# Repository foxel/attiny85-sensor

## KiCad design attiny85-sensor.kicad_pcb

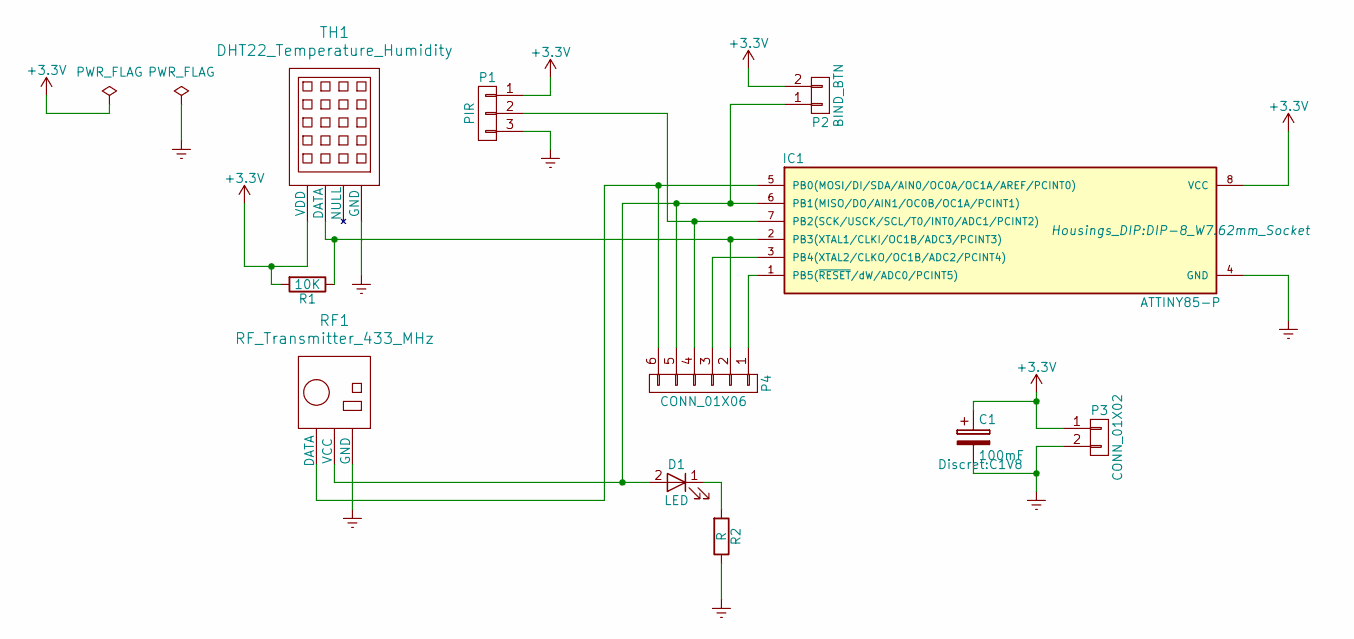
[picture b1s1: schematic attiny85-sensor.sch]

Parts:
C1: 100mF; C1V8
D1: LED; LED-3MM
IC1: ATTINY85-P; DIP-8_W7.62mm_Socket
P1: PIR; Pin_Header_Straight_1x03
P2: BIND_BTN; Pin_Header_Straight_1x02
P3: CONN_01X02; Pin_Header_Straight_1x02
P4: CONN_01X06; SMD_Pads
R1: 10K; R1
R2: R; R1
RF1: RF_Transmitter_433_MHz; RF_Transmitter_433_MHz_4PIN
TH1: DHT22_Temperature_Humidity

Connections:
+3V3: C1.1, IC1.8 (VCC), P1.1, P2.2, P3.1, R1.2, TH1.1 (VDD)
Earth: C1.2, IC1.4 (GND), P1.3, P3.2, R2.1, RF1.3 (GND), TH1.4 (GND)
unnamed: D1.1 (K), R2.2
unnamed: D1.2 (A), IC1.6 (PB1(MISO/DO/AIN1/OC0B/OC1A/PCINT1)), P2.1, P4.5, RF1.2 (VCC)
unnamed: IC1.1 (PB5(~RESET~/dW/ADC0/PCINT5)), P4.1
unnamed: IC1.2 (PB3(XTAL1/CLKI/OC1B/ADC3/PCINT3)), P4.2, R1.1, TH1.2 (DATA)
unnamed: IC1.3 (PB4(XTAL2/CLKO/OC1B/ADC2/PCINT4)), P4.3
unnamed: IC1.5 (PB0(MOSI/DI/SDA/AIN0/OC0A/OC1A/AREF/PCI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), P4.6, RF1.1 (DATA)
unnamed: IC1.7 (PB2(SCK/USCK/SCL/T0/INT0/ADC1/PCINT2)), P1.2, P4.4

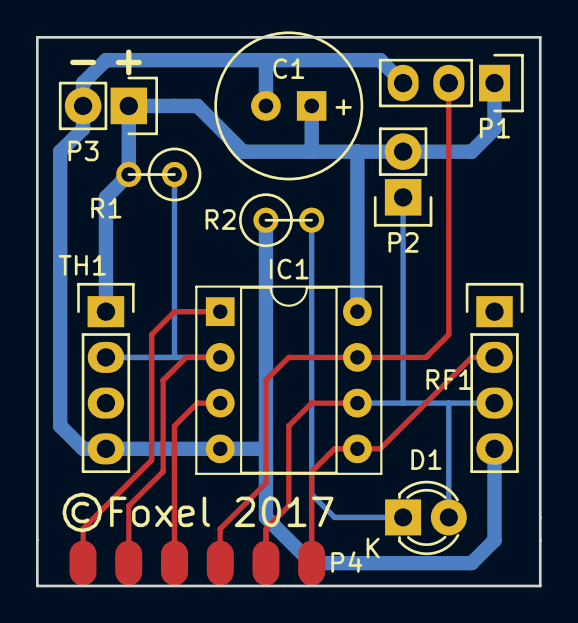
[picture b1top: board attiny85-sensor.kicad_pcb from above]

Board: 2 copper layers, 27.9 x 30.5 mm, 11 parts (0 on the bottom side), 9 nets.

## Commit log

2017-09-27 initial
2017-09-27 Socket for the chip
2019-01-05 Updated to comply newest library - stability fix
2019-01-05 Firmware source
2020-11-09 2020 updates

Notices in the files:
attiny85-sensor.kicad_pcb:
©Foxel 2017
